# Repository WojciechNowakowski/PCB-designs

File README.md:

# PCB-designs
Container for PCB designs created by me in KiCad.

1. "Licznik rowerowy Atxmega" - double sided PCB for a bike speed-o-meter designed by me with AtXmega used as the brain.
2. "MINI LINEFOLLOWER" - PCB design for a miniature linefollowing robot without microcontroller, 3D model:https://github.com/WojciechNowakowski/3D-Models/tree/master/MINI%20LF
3.

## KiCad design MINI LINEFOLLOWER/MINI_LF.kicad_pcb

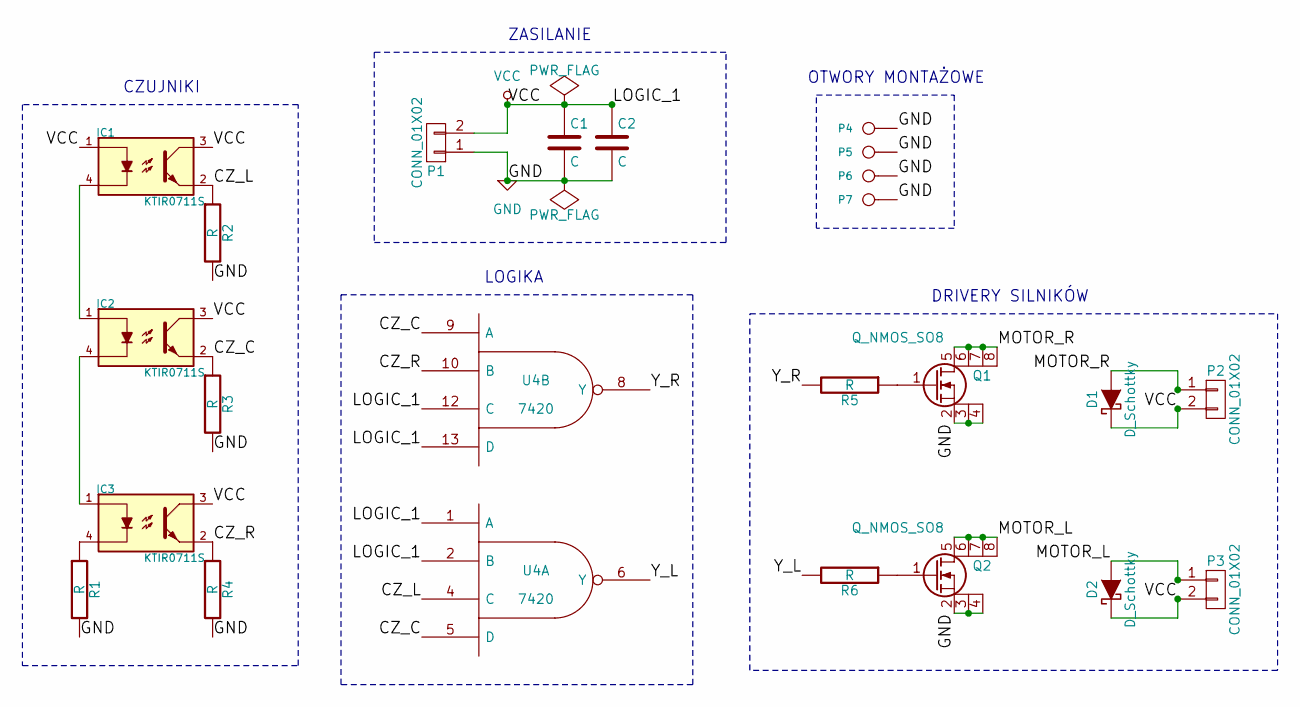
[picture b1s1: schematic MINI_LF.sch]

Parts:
C1, C2: C; C_0805_HandSoldering
D1, D2: D_Schottky; MELF_Handsoldering
IC1, IC2, IC3: KTIR0711S
P1, P2, P3: CONN_01X02; Pin_Header_Straight_1x02
P4, P5, P6, P7: CONN_1
Q1, Q2: Q_NMOS_SO8; SO-8
R1, R2, R3, R4, R5, R6: R; R_0805_HandSoldering
U4: 7420; DIP-14_W7.62mm_LongPads

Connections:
/CZ_L: IC1.2, R2.1, U4.4 (C)
/CZ_R: IC3.2, R4.1, U4.10 (B)
/CZ_Ś: IC2.2, R3.1, U4.5 (D), U4.9 (A)
/MOTOR_L: D2.2 (A), P3.1, Q2.5 (D), Q2.6 (D), Q2.7 (D), Q2.8 (D)
/MOTOR_R: D1.2 (A), P2.1, Q1.5 (D), Q1.6 (D), Q1.7 (D), Q1.8 (D)
/Y_L: R6.2, U4.6 (Y)
/Y_R: R5.2, U4.8 (Y)
GND: C1.2, C2.2, P1.1, P4.1, P5.1, P6.1, P7.1, Q1.2 (S), Q1.3 (S), Q1.4 (S), Q2.2 (S), Q2.3 (S), Q2.4 (S), R1.2, R2.2, R3.2, R4.2, U4.7 (GND)
unnamed: IC1.4, IC2.1
unnamed: IC2.4, IC3.1
unnamed: IC3.4, R1.1
unnamed: Q1.1 (G), R5.1
unnamed: Q2.1 (G), R6.1
VCC: C1.1, C2.1, D1.1 (K), D2.1 (K), IC1.1, IC1.3, IC2.3, IC3.3, P1.2, P2.2, P3.2, U4.1 (A), U4.2 (B), U4.12 (C), U4.13 (D), U4.14 (VCC)

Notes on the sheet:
ZASILANIE
LOGIKA
CZUJNIKI
OTWORY MONTAŻOWE
DRIVERY SILNIKÓW

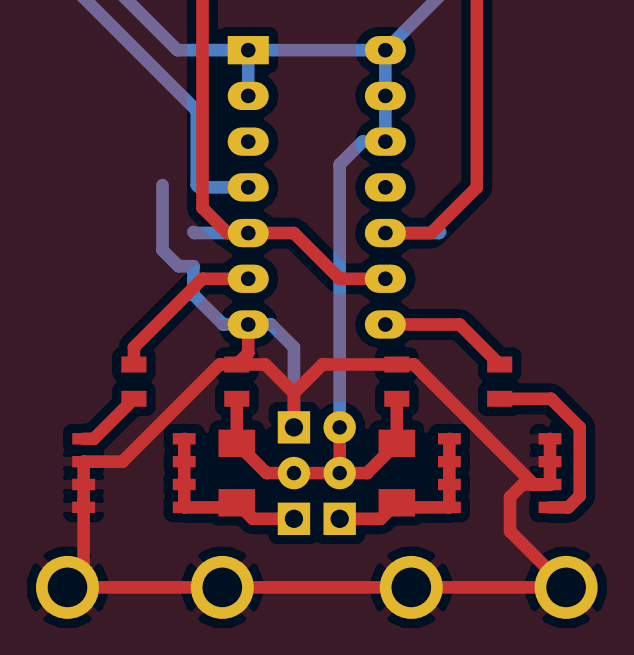
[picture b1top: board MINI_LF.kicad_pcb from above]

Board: 2 copper layers, 23 parts (0 on the bottom side), 14 nets.

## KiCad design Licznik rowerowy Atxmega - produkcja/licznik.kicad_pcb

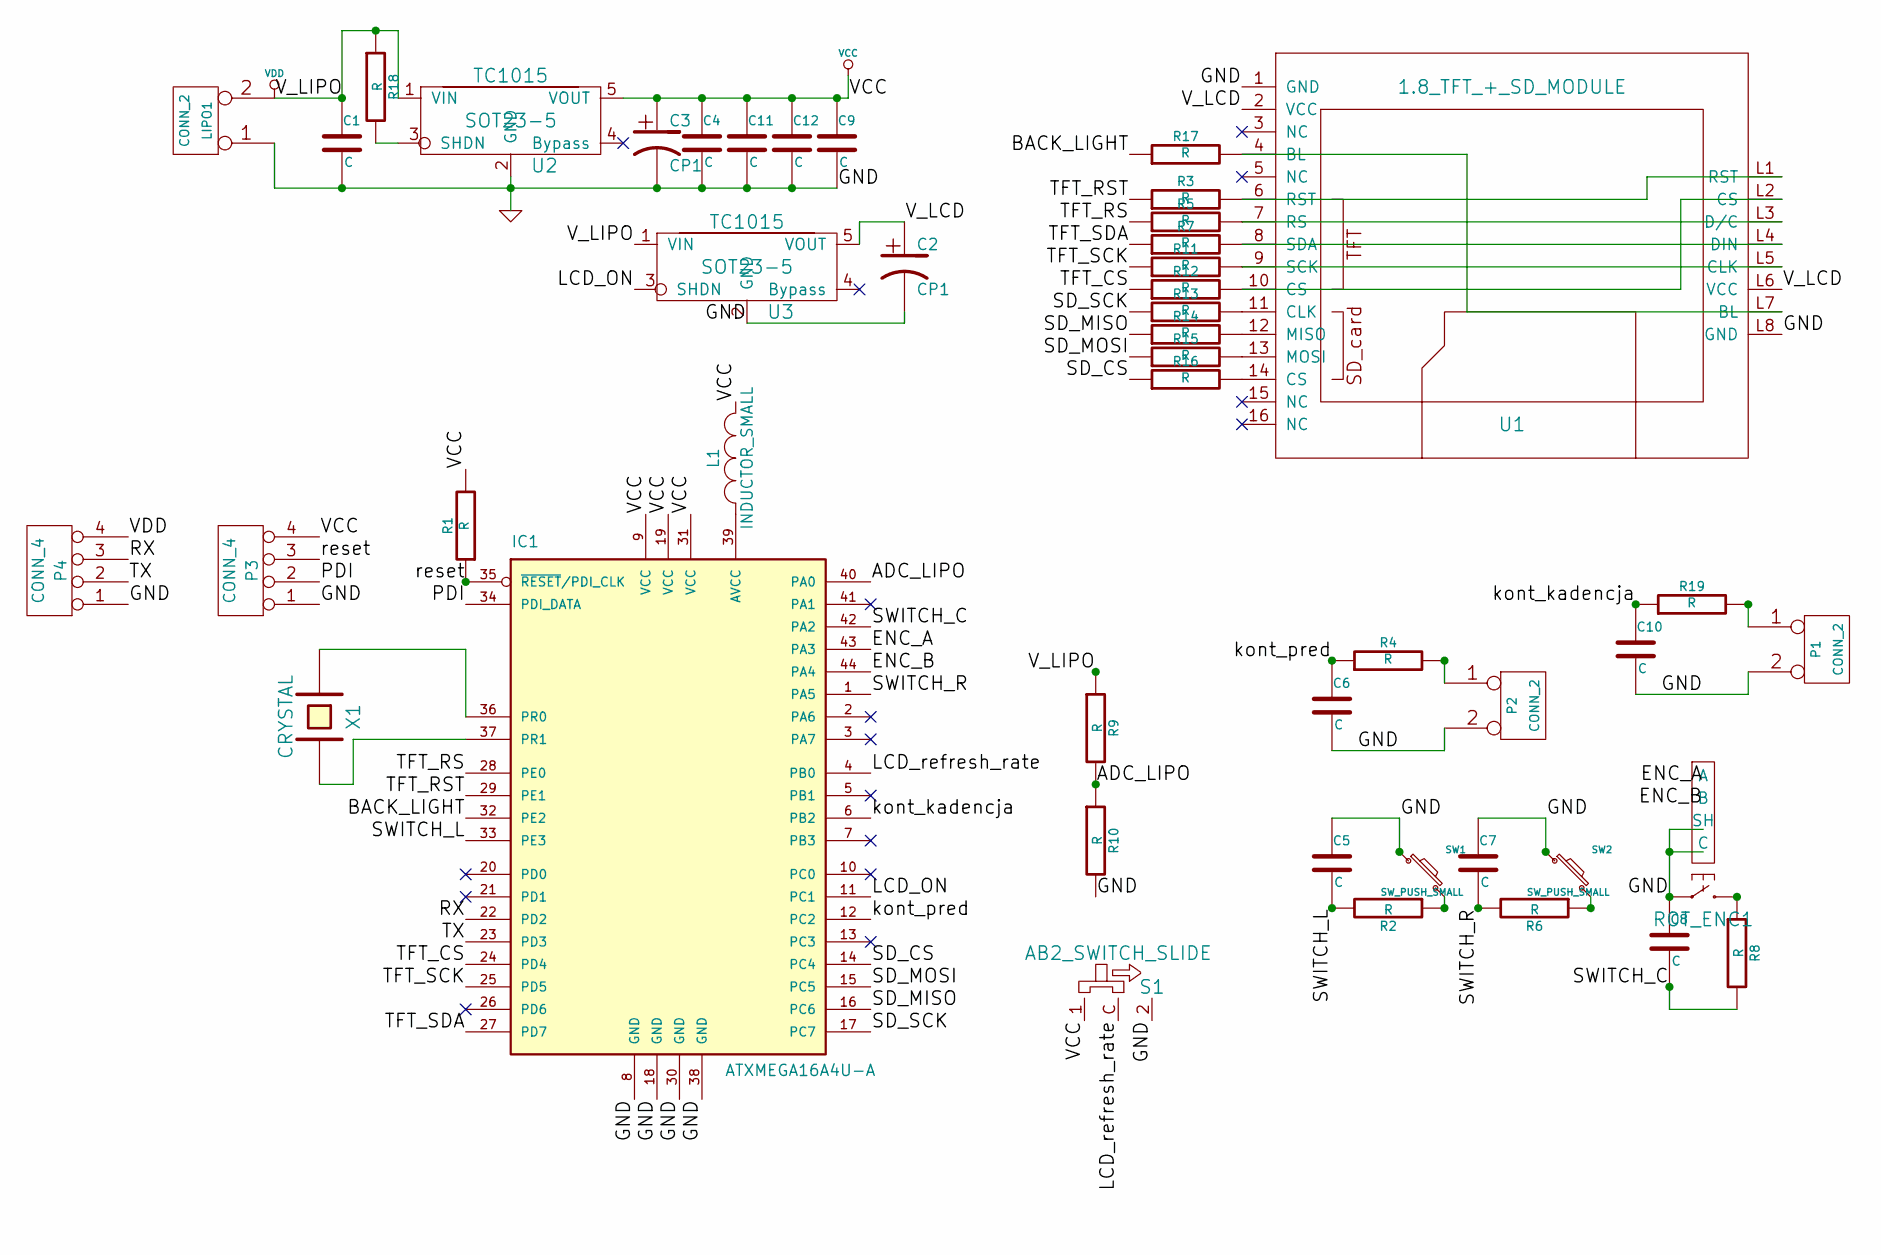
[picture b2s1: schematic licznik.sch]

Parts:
C1, C4, C5, C6, C7, C8, C9, C10, C11, C12: C
C2, C3: CP1
IC1: ATXMEGA16A4U-A; TQFP44
L1: INDUCTOR_SMALL
LIPO1: CONN_2
P1, P2: CONN_2
P3, P4: CONN_4
R1, R2, R3, R4, R5, R6, R7, R8, R9, R10, R11, R12, R13, R14, R15, R16, R17, R18, R19: R
ROT_ENC1: AB2_ROTARY_ENCODER_W_SW
S1: AB2_SWITCH_SLIDE
SW1, SW2: SW_PUSH_SMALL
U1: 1.8_TFT_+_SD_MODULE
U2, U3: TC1015; SOT23-5
X1: CRYSTAL

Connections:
/ADC_LIPO: IC1.40 (PA0), R9.2, R10.1
/BACK_LIGHT: IC1.32 (PE2), R17.1
/ENC_A: IC1.43 (PA3), ROT_ENC1.1 (A)
/ENC_B: IC1.44 (PA4), ROT_ENC1.3 (B)
/LCD_ON: IC1.11 (PC1), U3.3 (SHDN)
/LCD_refresh_rate: IC1.4 (PB0), S1.C
/PDI: IC1.34 (PDI_DATA), P3.2
/RX: IC1.22 (PD2), P4.3
/SD_CS: IC1.14 (PC4), R16.1
/SD_MISO: IC1.16 (PC6), R14.1
/SD_MOSI: IC1.15 (PC5), R15.1
/SD_SCK: IC1.17 (PC7), R13.1
/SWITCH_C: C8.2, IC1.42 (PA2), R8.2
/SWITCH_L: C5.2, IC1.33 (PE3), R2.2
/SWITCH_R: C7.2, IC1.1 (PA5), R6.2
/TFT_CS: IC1.24 (PD4), R12.1
/TFT_RS: IC1.28 (PE0), R5.1
/TFT_RST: IC1.29 (PE1), R3.1
/TFT_SCK: IC1.25 (PD5), R11.1
/TFT_SDA: IC1.27 (PD7), R7.1
/TX: IC1.23 (PD3), P4.2
/V_LCD: C2.1, U1.2 (VCC), U1.L6 (VCC), U3.5 (VOUT)
/kont_kadencja: C10.1, IC1.6 (PB2), R19.1
/kont_pred: C6.1, IC1.12 (PC2), R4.1
/reset: IC1.35 (~RESET~/PDI_CLK), P3.3, R1.1
GND: C1.2, C2.2, C3.2, C4.2, C5.1, C6.2, C7.1, C8.1, C9.2, C10.2, C11.2, C12.2, IC1.8 (GND), IC1.18 (GND), IC1.30 (GND), IC1.38 (GND), LIPO1.1, P1.2 (PM), P2.2 (PM), P3.1, P4.1, R10.2, ROT_ENC1.2 (C), ROT_ENC1.4, ROT_ENC1.7 (SH), S1.2, SW1.1, SW2.1, U1.1 (GND), U1.L8 (GND), U2.2 (GND), U3.2 (GND)
unnamed: R13.2, U1.11 (CLK)
unnamed: R14.2, U1.12 (MISO)
unnamed: R15.2, U1.13 (MOSI)
unnamed: R16.2, U1.14 (CS)
unnamed: R12.2, U1.10 (CS), U1.L2 (CS)
unnamed: R3.2, U1.6 (RST), U1.L1 (RST)
unnamed: R17.2, U1.4 (BL), U1.L7 (BL)
unnamed: R11.2, U1.9 (SCK), U1.L5 (CLK)
unnamed: R8.1, ROT_ENC1.6
unnamed: P1.1, R19.2
unnamed: R7.2, U1.8 (SDA), U1.L4 (DIN)
unnamed: R5.2, U1.7 (RS), U1.L3 (D/C)
unnamed: R18.2, U2.3 (SHDN)
unnamed: IC1.39 (AVCC), L1.1
unnamed: P2.1, R4.2
unnamed: IC1.37 (PR1), X1.2
unnamed: IC1.36 (PR0), X1.1
unnamed: R2.1, SW1.2
unnamed: R6.1, SW2.2
VCC: C3.1, C4.1, C9.1, C11.1, C12.1, IC1.9 (VCC), IC1.19 (VCC), IC1.31 (VCC), L1.2, P3.4, R1.2, S1.1, U2.5 (VOUT)
VDD: C1.1, LIPO1.2 (PM), P4.4, R9.1, R18.1, U2.1 (VIN), U3.1 (VIN)

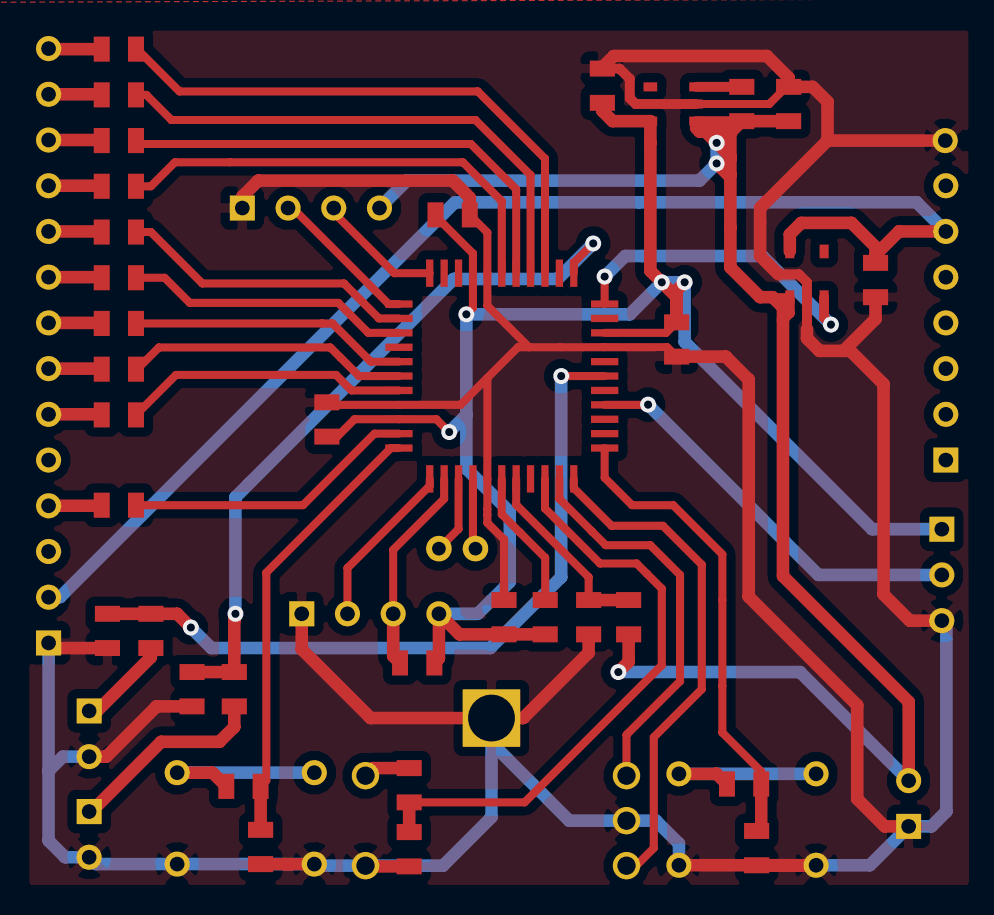
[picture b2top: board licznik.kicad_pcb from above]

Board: 2 copper layers, 46 parts (0 on the bottom side), 47 nets.

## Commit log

2020-04-16 Add License file
2020-04-16 Add PCB design of bike speedo-meter
2020-05-14 Add photos of the PCB
2020-05-14 Add resized photos
2020-06-01 Add photo of my boards
2020-06-01 Resize of overview photo
2020-06-01 Add PCB design of miniature linefollower
